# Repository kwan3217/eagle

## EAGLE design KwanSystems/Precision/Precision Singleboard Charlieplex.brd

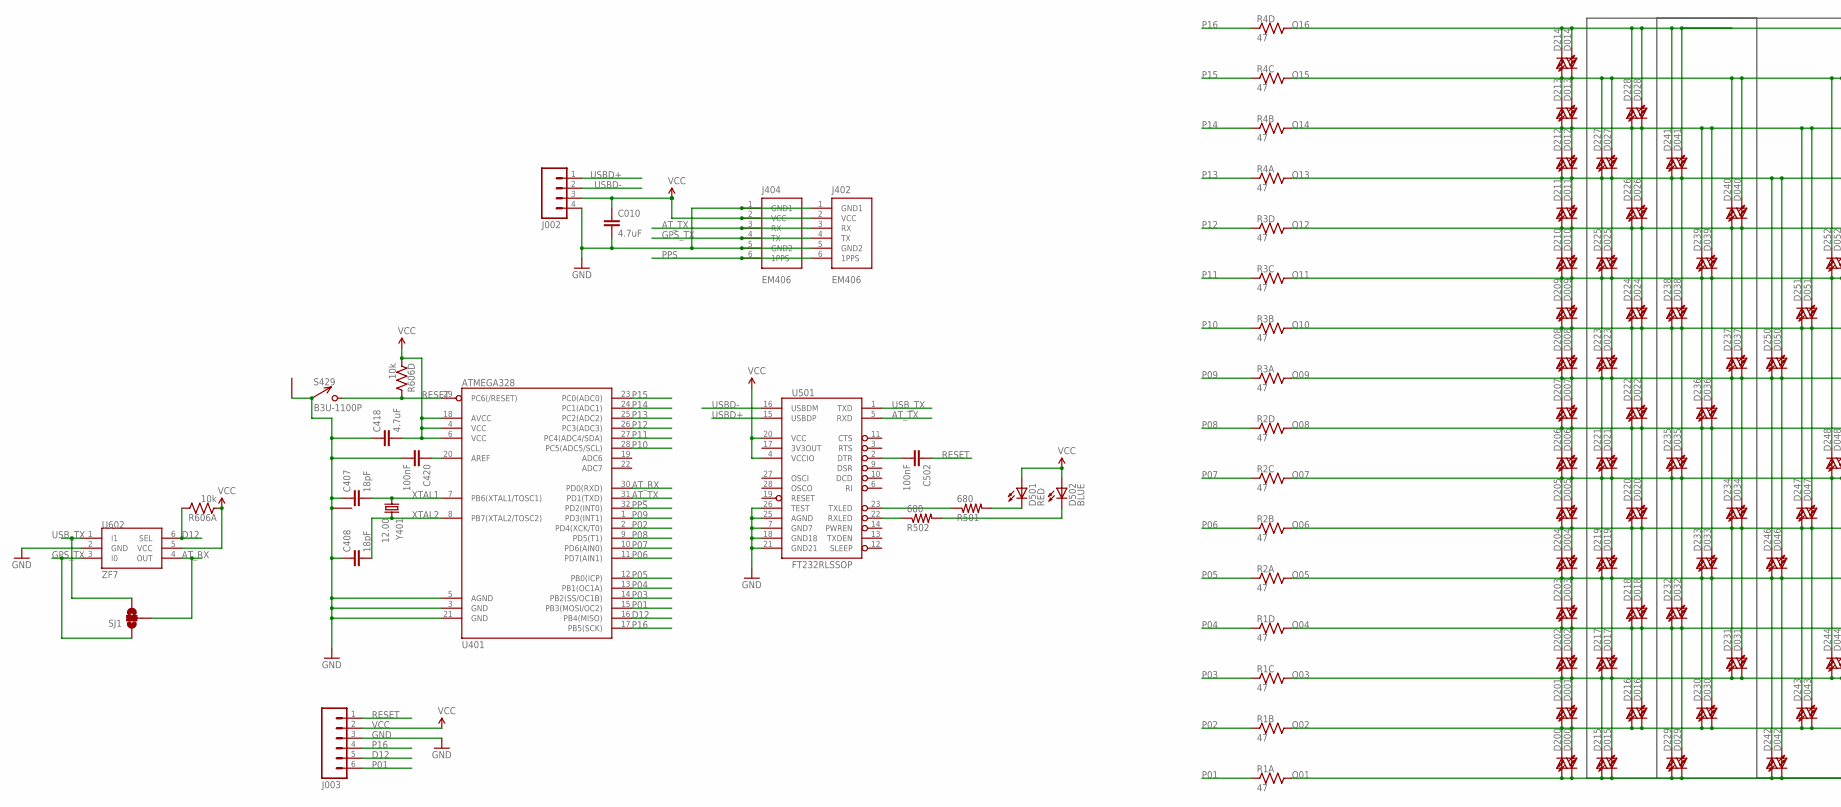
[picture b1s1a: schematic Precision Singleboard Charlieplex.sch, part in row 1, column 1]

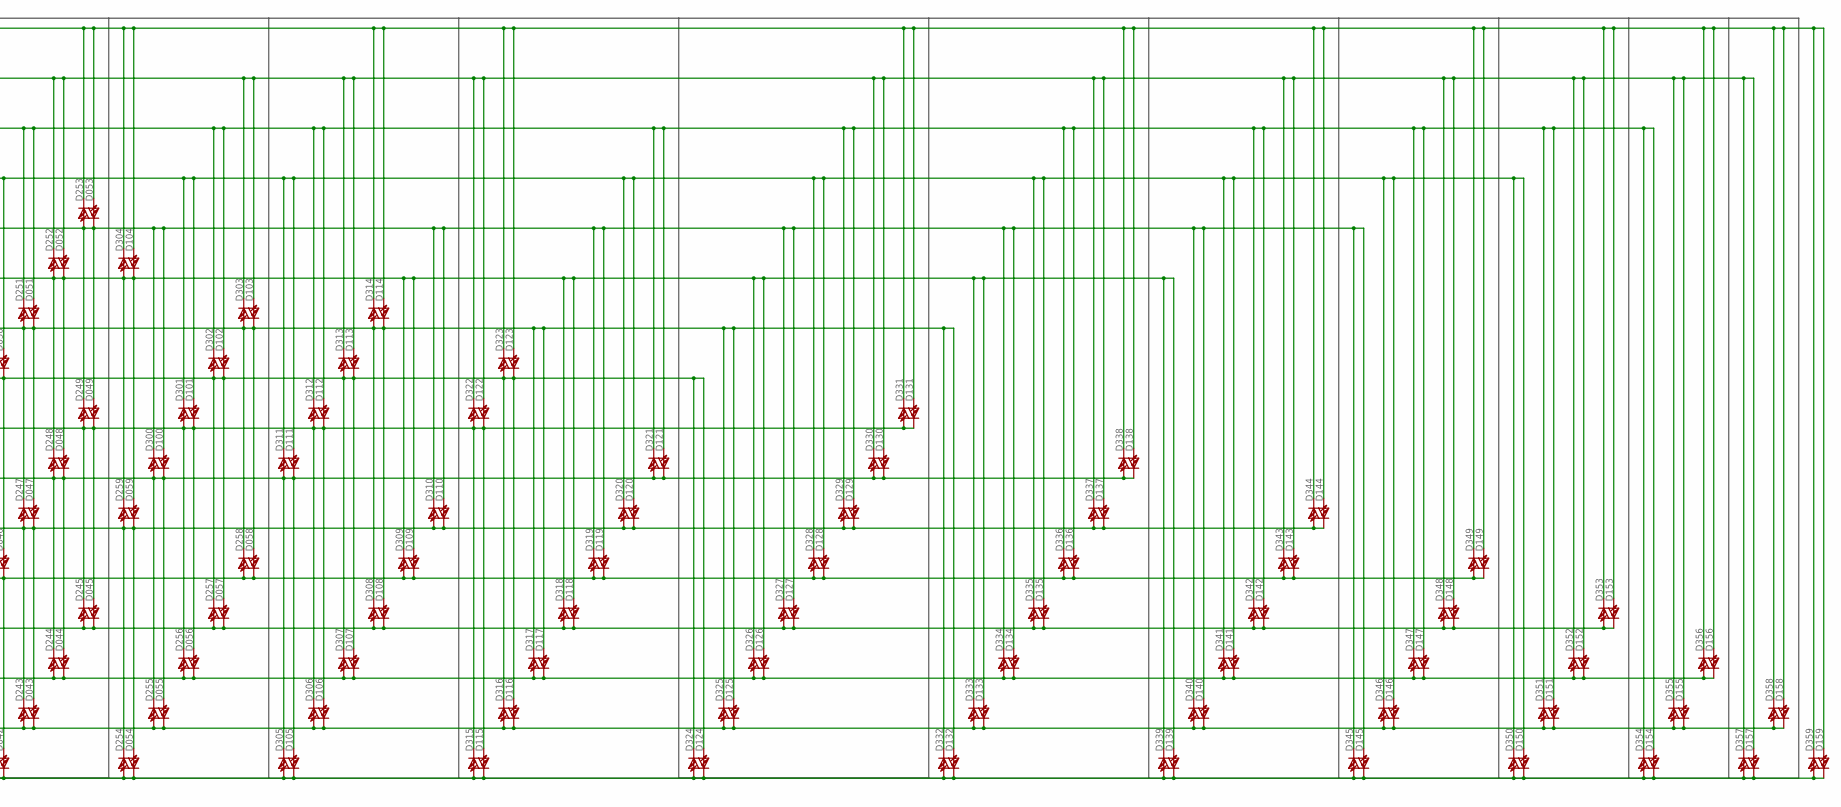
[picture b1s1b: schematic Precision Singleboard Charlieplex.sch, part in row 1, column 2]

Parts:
C010, C418: 4.7uF; 0603-CAP
C407, C408: 18pF; 0603-CAP
C420, C502: 100nF; 0603-CAP
D000, D001, D002, D003, D004, D005, D006, D007, D008, D009, D010, D011, D012, D013, D014, D015, D016, D017, D018, D019, D020, D021, D022, D023, D024, D025, D026, D027, D028, D029, D030, D031, D032, D033, D034, D035, D036, D037, D038, D039, D040, D041, D042, D043, D044, D045, D046, D047, D048, D049, D050, D051, D052, D053, D054, D055, D056, D057, D058, D059, D100, D101, D102, D103, D104, D105, D106, D107, D108, D109, D110, D111, D112, D113, D114, D115, D116, D117, D118, D119, D120, D121, D122, D123, D124, D125, D126, D127, D128, D129, D130, D131, D132, D133, D134, D135, D136, D137, D138, D139, D140, D141, D142, D143, D144, D145, D146, D147, D148, D149, D150, D151, D152, D153, D154, D155, D156, D157, D158, D159, D200, D201, D202, D203, D204, D205, D206, D207, D208, D209, D210, D211, D212, D213, D214, D215, D216, D217, D218, D219, D220, D221, D222, D223, D224, D225, D226, D227, D228, D229, D230, D231, D232, D233, D234, D235, D236, D237, D238, D239, D240, D241, D242, D243, D244, D245, D246, D247, D248, D249, D250, D251, D252, D253, D254, D255, D256, D257, D258, D259, D300, D301, D302, D303, D304, D305, D306, D307, D308, D309, D310, D311, D312, D313, D314, D315, D316, D317, D318, D319, D320, D321, D322, D323, D324, D325, D326, D327, D328, D329, D330, D331, D332, D333, D334, D335, D336, D337, D338, D339, D340, D341, D342, D343, D344, D345, D346, D347, D348, D349, D350, D351, D352, D353, D354, D355, D356, D357, D358, D359: HOUR; LED-0603
D501: RED; LED-0603
D502: BLUE; LED-0603
J002: M04PTH; 1X04
J003: M06SIP; 1X06
J402, J404: EM406
R1, R2, R3, R4: 47; CRA04
R501, R502: 680; 0603-RES
R606: 10k; CRA04
S429: B3U-1100P
SJ1: SOLDERJUMPER_2WAYS; SJ_3
U401: ATMEGA328; TQFP32-08
U501: FT232RLSSOP; SSOP28DB
U602: ZF7; SC-70-6
Y401: 12.00; CRYSTAL_SMD

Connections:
AREF: C420.1, U401.20 (AREF)
AT_RX: SJ1.2, U401.30 (PD0(RXD)), U602.4 (OUT)
AT_TX: J402.3 (RX), J404.3 (RX), U401.31 (PD1(TXD)), U501.5 (RXD)
D12: J003.5, R606.8 (2), U401.16 (PB4(MISO)), U602.6 (SEL)
GND: C010.2, C407.1, C408.1, C418.1, C420.2, J002.4, J003.3, J402.1 (GND1), J402.5 (GND2), J404.1 (GND1), J404.5 (GND2), S429.P$1 (1), S429.P$3 (1), U401.3 (GND), U401.5 (AGND), U401.21 (GND), U501.7 (GND7), U501.18 (GND18), U501.21 (GND21), U501.25 (AGND), U501.26 (TEST), U602.2 (GND), Y401.2 (1), Y401.4 (1)
GPS_TX: J402.4 (TX), J404.4 (TX), SJ1.1, U602.3 (I0)
unnamed: C502.2, U501.2 (DTR)
unnamed: D501.C, R501.2
unnamed: R501.1, U501.23 (TXLED)
unnamed: R502.1, U501.22 (RXLED)
unnamed: D502.C, R502.2
P01: J003.6, R1.1, U401.15 (PB3(MOSI/OC2))
P02: R1.2 (1), U401.2 (PD4(XCK/T0))
P03: R1.3 (1), U401.14 (PB2(SS/OC1B))
P04: R1.4 (1), U401.13 (PB1(OC1A))
P05: R2.1, U401.12 (PB0(ICP))
P06: R2.2 (1), U401.11 (PD7(AIN1))
P07: R2.3 (1), U401.10 (PD6(AIN0))
P08: R2.4 (1), U401.9 (PD5(T1))
P09: R3.1, U401.1 (PD3(INT1))
P10: R3.2 (1), U401.28 (PC5(ADC5/SCL))
P11: R3.3 (1), U401.27 (PC4(ADC4/SDA))
P12: R3.4 (1), U401.26 (PC3(ADC3))
P13: R4.1, U401.25 (PC2(ADC2))
P14: R4.2 (1), U401.24 (PC1(ADC1))
P15: R4.3 (1), U401.23 (PC0(ADC0))
P16: J003.4, R4.4 (1), U401.17 (PB5(SCK))
PPS: J402.6 (1PPS), J404.6 (1PPS), U401.32 (PD2(INT0))
Q01: D000.C, D015.C, D029.C, D042.C, D054.C, D105.C, D115.C, D124.C, D132.C, D139.C, D145.C, D150.C, D154.C, D157.C, D159.C, D200.A, D215.A, D229.A, D242.A, D254.A, D305.A, D315.A, D324.A, D332.A, D339.A, D345.A, D350.A, D354.A, D357.A, D359.A, R1.8 (2)
Q02: D000.A, D001.C, D016.C, D030.C, D043.C, D055.C, D106.C, D116.C, D125.C, D133.C, D140.C, D146.C, D151.C, D155.C, D158.C, D200.C, D201.A, D216.A, D230.A, D243.A, D255.A, D306.A, D316.A, D325.A, D333.A, D340.A, D346.A, D351.A, D355.A, D358.A, R1.7 (2)
Q03: D001.A, D002.C, D015.A, D017.C, D031.C, D044.C, D056.C, D107.C, D117.C, D126.C, D134.C, D141.C, D147.C, D152.C, D156.C, D201.C, D202.A, D215.C, D217.A, D231.A, D244.A, D256.A, D307.A, D317.A, D326.A, D334.A, D341.A, D347.A, D352.A, D356.A, R1.6 (2)
Q04: D002.A, D003.C, D016.A, D018.C, D029.A, D032.C, D045.C, D057.C, D108.C, D118.C, D127.C, D135.C, D142.C, D148.C, D153.C, D202.C, D203.A, D216.C, D218.A, D229.C, D232.A, D245.A, D257.A, D308.A, D318.A, D327.A, D335.A, D342.A, D348.A, D353.A, R1.5 (2)
Q05: D003.A, D004.C, D017.A, D019.C, D030.A, D033.C, D042.A, D046.C, D058.C, D109.C, D119.C, D128.C, D136.C, D143.C, D149.C, D203.C, D204.A, D217.C, D219.A, D230.C, D233.A, D242.C, D246.A, D258.A, D309.A, D319.A, D328.A, D336.A, D343.A, D349.A, R2.8 (2)
Q06: D004.A, D005.C, D018.A, D020.C, D031.A, D034.C, D043.A, D047.C, D054.A, D059.C, D110.C, D120.C, D129.C, D137.C, D144.C, D204.C, D205.A, D218.C, D220.A, D231.C, D234.A, D243.C, D247.A, D254.C, D259.A, D310.A, D320.A, D329.A, D337.A, D344.A, R2.7 (2)
Q07: D005.A, D006.C, D019.A, D021.C, D032.A, D035.C, D044.A, D048.C, D055.A, D100.C, D105.A, D111.C, D121.C, D130.C, D138.C, D205.C, D206.A, D219.C, D221.A, D232.C, D235.A, D244.C, D248.A, D255.C, D300.A, D305.C, D311.A, D321.A, D330.A, D338.A, R2.6 (2)
Q08: D006.A, D007.C, D020.A, D022.C, D033.A, D036.C, D045.A, D049.C, D056.A, D101.C, D106.A, D112.C, D115.A, D122.C, D131.C, D206.C, D207.A, D220.C, D222.A, D233.C, D236.A, D245.C, D249.A, D256.C, D301.A, D306.C, D312.A, D315.C, D322.A, D331.A, R2.5 (2)
Q09: D007.A, D008.C, D021.A, D023.C, D034.A, D037.C, D046.A, D050.C, D057.A, D102.C, D107.A, D113.C, D116.A, D123.C, D124.A, D207.C, D208.A, D221.C, D223.A, D234.C, D237.A, D246.C, D250.A, D257.C, D302.A, D307.C, D313.A, D316.C, D323.A, D324.C, R3.8 (2)
Q10: D008.A, D009.C, D022.A, D024.C, D035.A, D038.C, D047.A, D051.C, D058.A, D103.C, D108.A, D114.C, D117.A, D125.A, D132.A, D208.C, D209.A, D222.C, D224.A, D235.C, D238.A, D247.C, D251.A, D258.C, D303.A, D308.C, D314.A, D317.C, D325.C, D332.C, R3.7 (2)
Q11: D009.A, D010.C, D023.A, D025.C, D036.A, D039.C, D048.A, D052.C, D059.A, D104.C, D109.A, D118.A, D126.A, D133.A, D139.A, D209.C, D210.A, D223.C, D225.A, D236.C, D239.A, D248.C, D252.A, D259.C, D304.A, D309.C, D318.C, D326.C, D333.C, D339.C, R3.6 (2)
Q12: D010.A, D011.C, D024.A, D026.C, D037.A, D040.C, D049.A, D053.C, D100.A, D110.A, D119.A, D127.A, D134.A, D140.A, D145.A, D210.C, D211.A, D224.C, D226.A, D237.C, D240.A, D249.C, D253.A, D300.C, D310.C, D319.C, D327.C, D334.C, D340.C, D345.C, R3.5 (2)
Q13: D011.A, D012.C, D025.A, D027.C, D038.A, D041.C, D050.A, D101.A, D111.A, D120.A, D128.A, D135.A, D141.A, D146.A, D150.A, D211.C, D212.A, D225.C, D227.A, D238.C, D241.A, D250.C, D301.C, D311.C, D320.C, D328.C, D335.C, D341.C, D346.C, D350.C, R4.8 (2)
Q14: D012.A, D013.C, D026.A, D028.C, D039.A, D051.A, D102.A, D112.A, D121.A, D129.A, D136.A, D142.A, D147.A, D151.A, D154.A, D212.C, D213.A, D226.C, D228.A, D239.C, D251.C, D302.C, D312.C, D321.C, D329.C, D336.C, D342.C, D347.C, D351.C, D354.C, R4.7 (2)
Q15: D013.A, D014.C, D027.A, D040.A, D052.A, D103.A, D113.A, D122.A, D130.A, D137.A, D143.A, D148.A, D152.A, D155.A, D157.A, D213.C, D214.A, D227.C, D240.C, D252.C, D303.C, D313.C, D322.C, D330.C, D337.C, D343.C, D348.C, D352.C, D355.C, D357.C, R4.6 (2)
Q16: D014.A, D028.A, D041.A, D053.A, D104.A, D114.A, D123.A, D131.A, D138.A, D144.A, D149.A, D153.A, D156.A, D158.A, D159.A, D214.C, D228.C, D241.C, D253.C, D304.C, D314.C, D323.C, D331.C, D338.C, D344.C, D349.C, D353.C, D356.C, D358.C, D359.C, R4.5 (2)
RESET: C502.1, J003.1, R606.5 (2), S429.P$2 (2), U401.29 (PC6(/RESET))
USBD+: J002.1, U501.15 (USBDP)
USBD-: J002.2, U501.16 (USBDM)
USB_TX: SJ1.3, U501.1 (TXD), U602.1 (I1)
VCC: C010.1, C418.2, D501.A, D502.A, J002.3, J003.2, J402.2 (VCC), J404.2 (VCC), R606.1, R606.4 (1), U401.4 (VCC), U401.6 (VCC), U401.18 (AVCC), U501.4 (VCCIO), U501.20 (VCC), U602.5 (VCC)
XTAL1: C407.2, U401.7 (PB6(XTAL1/TOSC1)), Y401.1
XTAL2: C408.2, U401.8 (PB7(XTAL2/TOSC2)), Y401.3 (2)

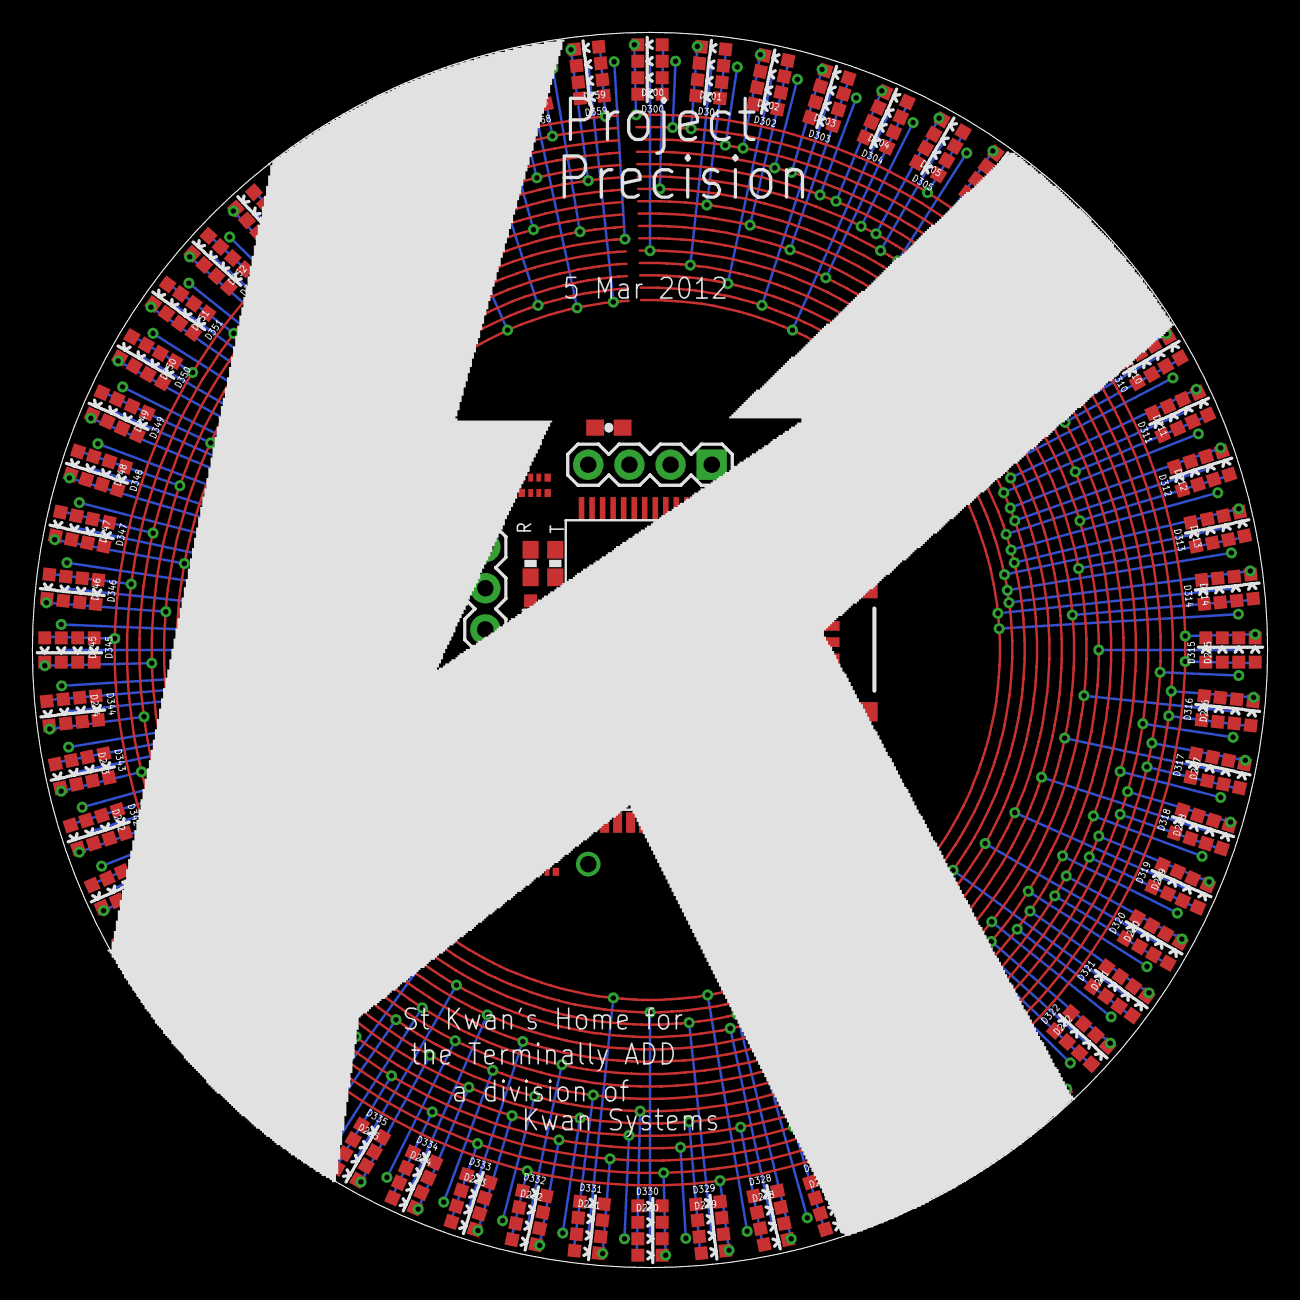
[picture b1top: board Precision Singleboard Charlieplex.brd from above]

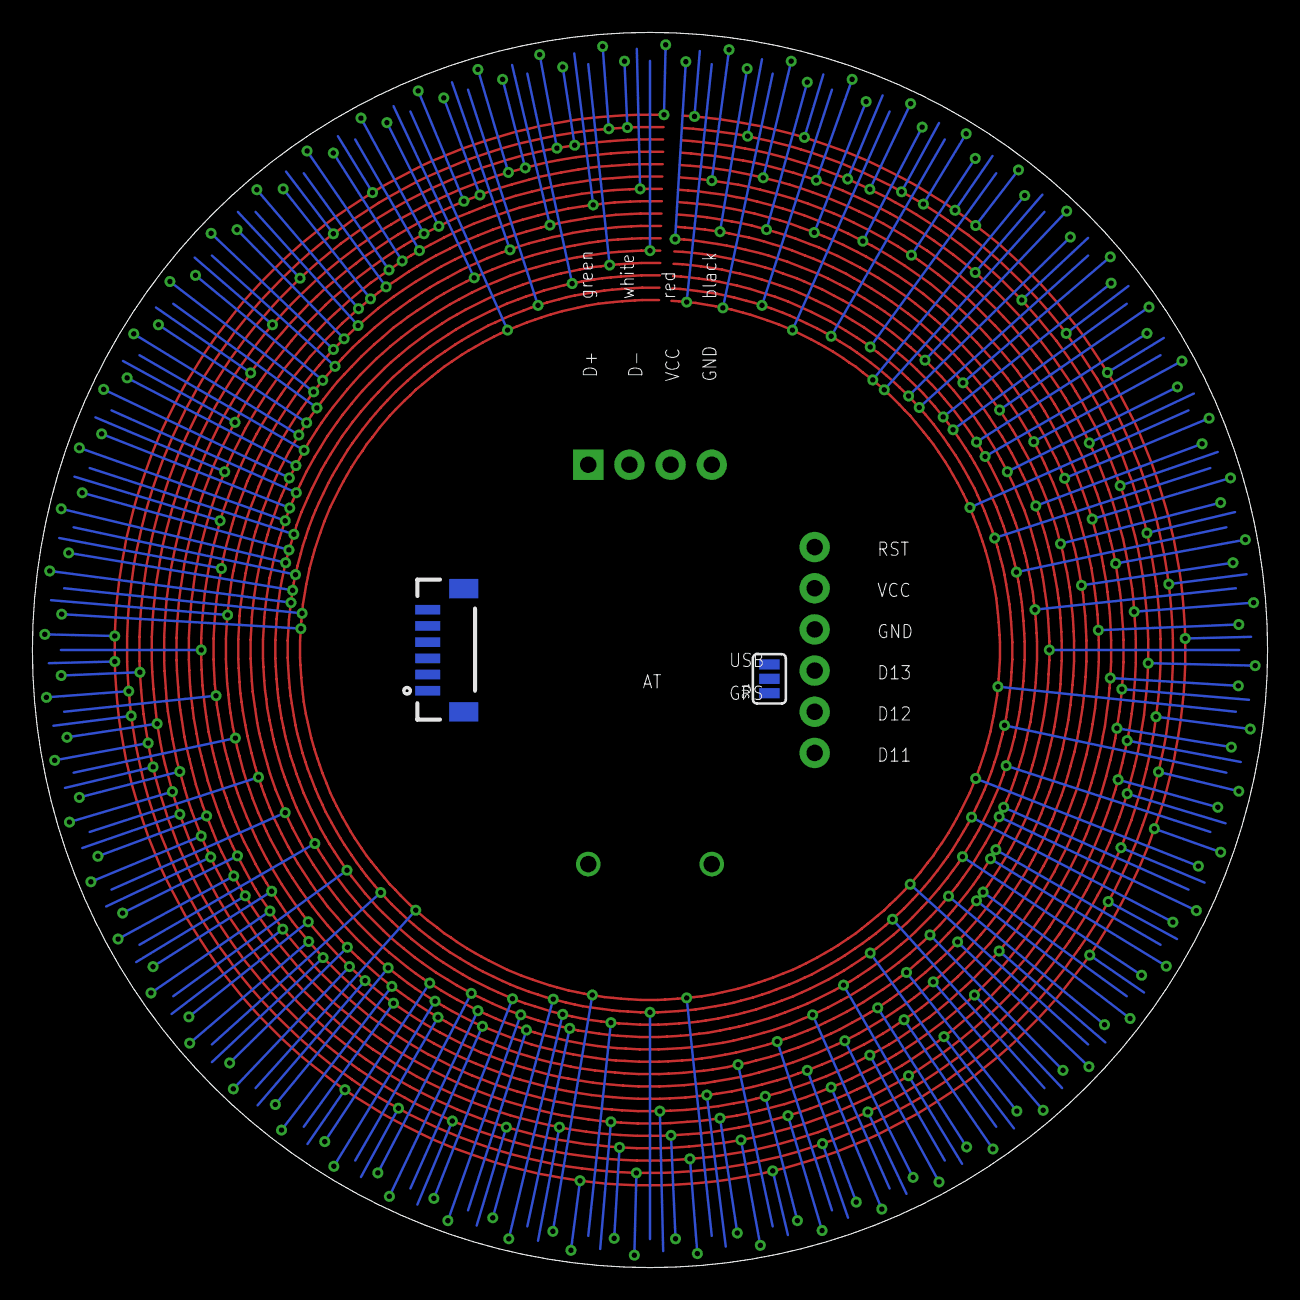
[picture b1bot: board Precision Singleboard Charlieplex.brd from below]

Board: 2 copper layers, 76.2 x 76.2 mm, 265 parts (2 on the bottom side), 51 nets.

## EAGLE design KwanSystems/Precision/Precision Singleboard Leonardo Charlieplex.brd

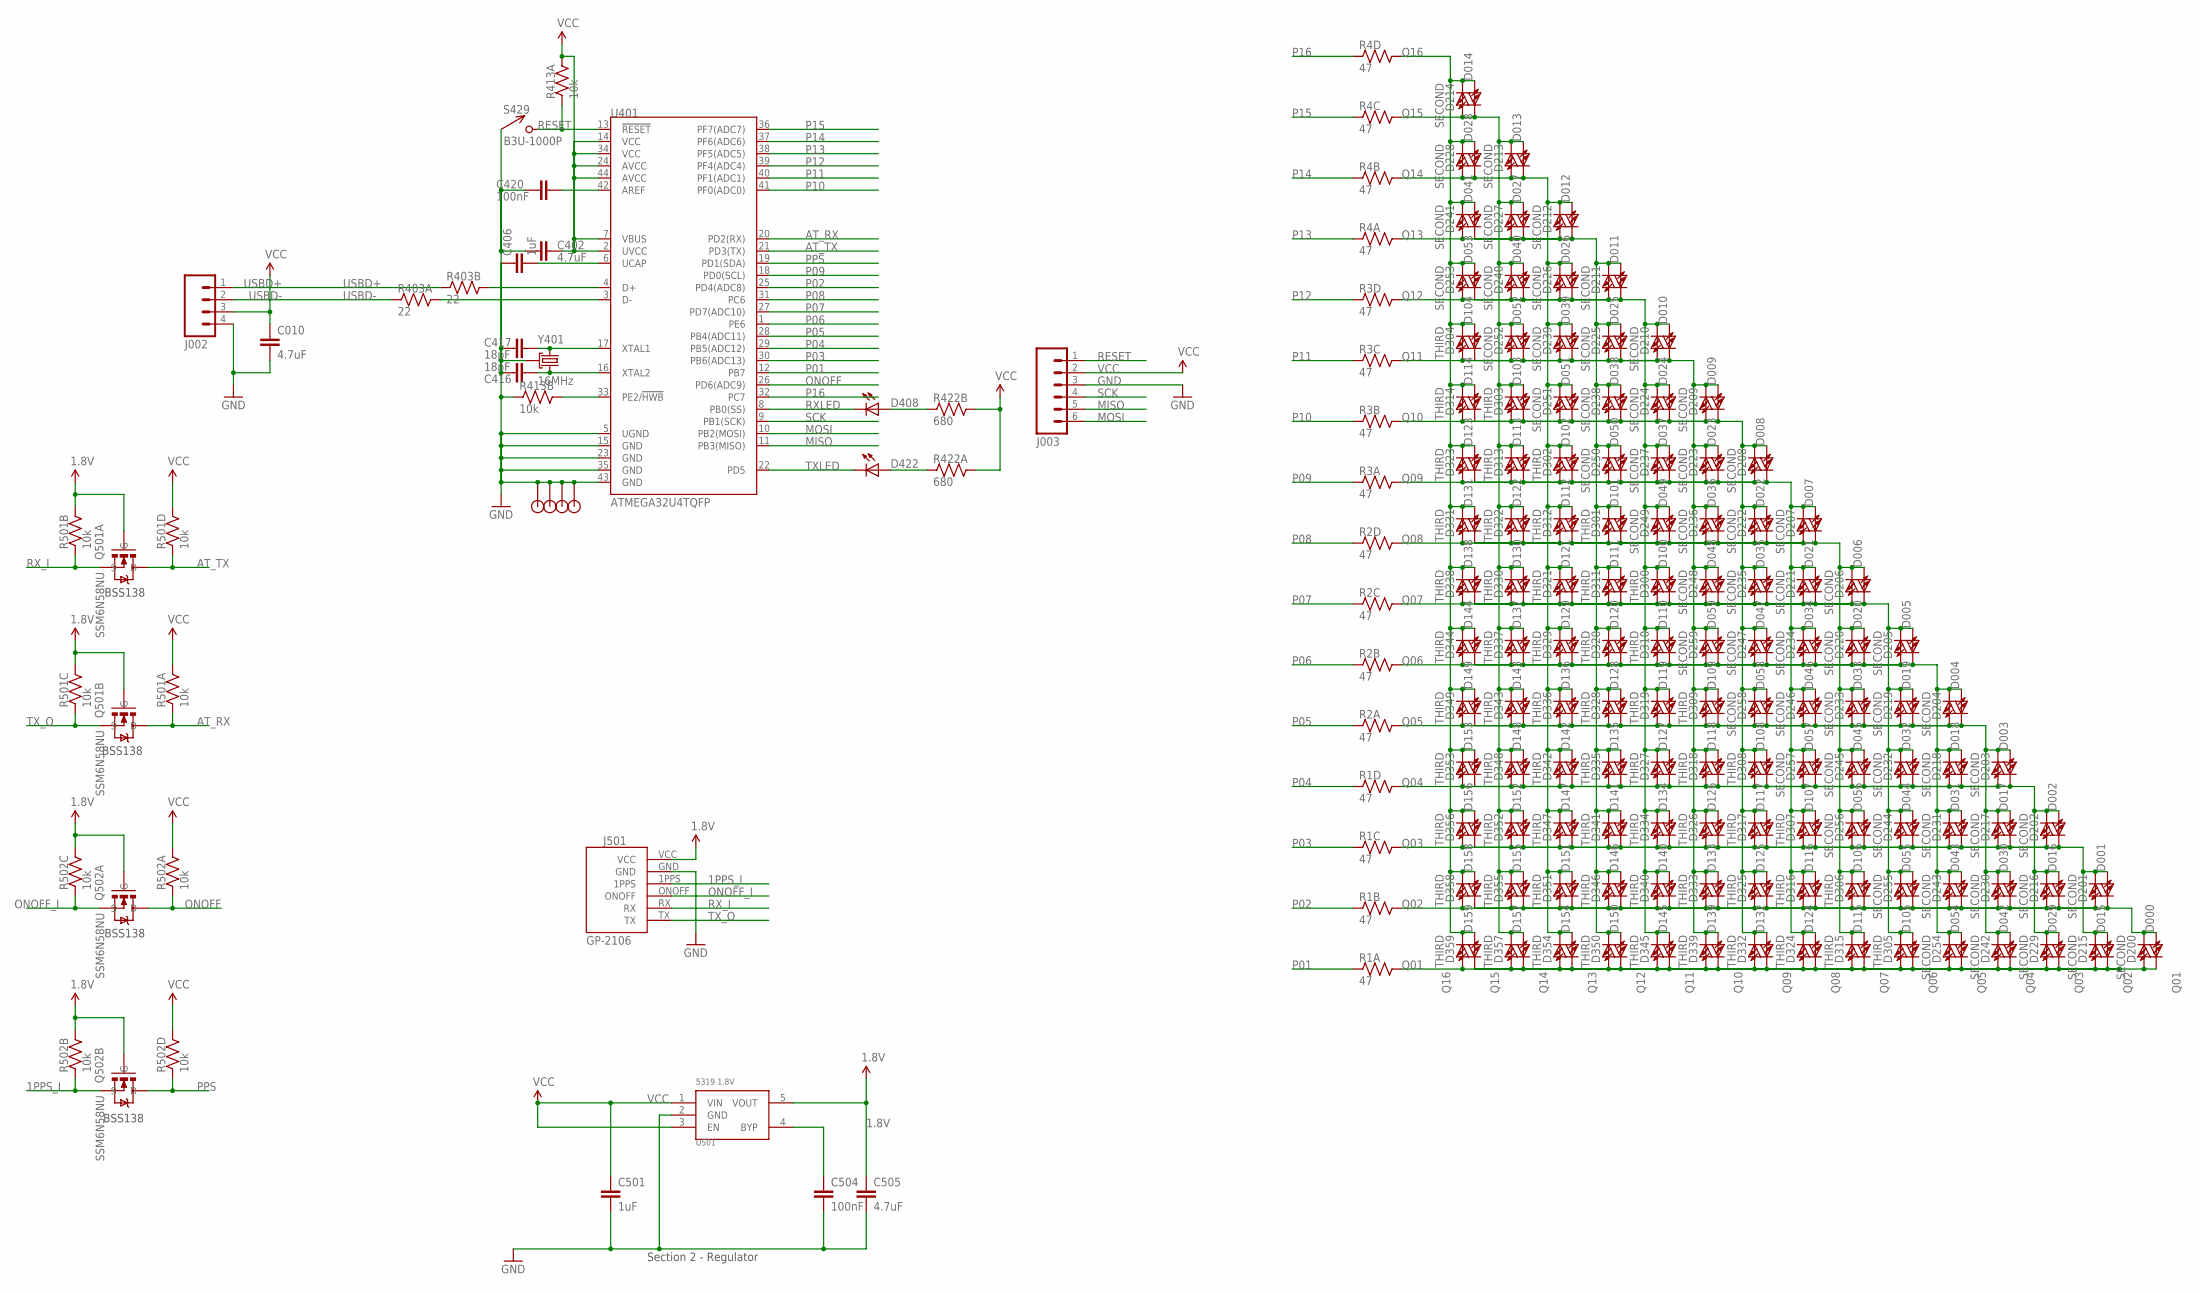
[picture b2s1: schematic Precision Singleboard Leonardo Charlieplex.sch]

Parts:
C010, C402: 4.7uF; 0603-CAP
C406, C501: 1uF; 0603-CAP; DIGIKEY 445-4114-1-ND
C416, C417: 18pF; 0603-CAP
C420: 100nF; 0603-CAP
C504: 100nF; 0603-CAP; DIGIKEY 445-1265-1-ND
C505: 4.7uF; 0603-CAP; DIGIKEY 445-7395-1-ND
D000, D001, D002, D003, D004, D005, D006, D007, D008, D009, D010, D011, D012, D013, D014, D015, D016, D017, D018, D019, D020, D021, D022, D023, D024, D025, D026, D027, D028, D029, D030, D031, D032, D033, D034, D035, D036, D037, D038, D039, D040, D041, D042, D043, D044, D045, D046, D047, D048, D049, D050, D051, D052, D053, D054, D055, D056, D057, D058, D059: HOUR; LED-0603
D100, D101, D102, D103, D104, D105, D106, D107, D108, D109, D110, D111, D112, D113, D114, D115, D116, D117, D118, D119, D120, D121, D122, D123, D124, D125, D126, D127, D128, D129, D130, D131, D132, D133, D134, D135, D136, D137, D138, D139, D140, D141, D142, D143, D144, D145, D146, D147, D148, D149, D150, D151, D152, D153, D154, D155, D156, D157, D158, D159: MINUTE; LED-0603
D200, D201, D202, D203, D204, D205, D206, D207, D208, D209, D210, D211, D212, D213, D214, D215, D216, D217, D218, D219, D220, D221, D222, D223, D224, D225, D226, D227, D228, D229, D230, D231, D232, D233, D234, D235, D236, D237, D238, D239, D240, D241, D242, D243, D244, D245, D246, D247, D248, D249, D250, D251, D252, D253, D254, D255, D256, D257, D258, D259: SECOND; LED-0603
D300, D301, D302, D303, D304, D305, D306, D307, D308, D309, D310, D311, D312, D313, D314, D315, D316, D317, D318, D319, D320, D321, D322, D323, D324, D325, D326, D327, D328, D329, D330, D331, D332, D333, D334, D335, D336, D337, D338, D339, D340, D341, D342, D343, D344, D345, D346, D347, D348, D349, D350, D351, D352, D353, D354, D355, D356, D357, D358, D359: THIRD; LED-0603
D408: RED; LED-0603
D422: BLUE; LED-0603
J002: M04PTH; 1X04
J003: M06SIP; 1X06
J501: GP-2106
JP1, JP2, JP3, JP4: STANDOFF
Q501, Q502: SSM6N58NU; UDFN6
R1, R2, R3, R4: 47; CRA04
R403: 22; CRA02
R413: 10k; CRA02
R422: 680; CRA02
R501, R502: 10k; CRA04; DIGIKEY CRA4S810KCT-ND
S429: B3U-1000P
U401: ATMEGA32U4TQFP; SPARKFUN-DIGITALIC_TQFP44
U501: 5319 1.8V; SOT-23-5; DIGIKEY 576-1910-1-ND
Y401: 16MHz; CRYSTAL_SMD

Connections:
1.8V: C505.1, J501.VCC, Q501.2 (G), Q501.5 (G), Q502.2 (G), Q502.5 (G), R501.6 (2), R501.7 (2), R502.6 (2), R502.7 (2), U501.5 (VOUT)
1PPS_I: J501.1PPS, Q502.4 (S), R502.2 (1)
AREF: C420.1, U401.42 (AREF)
AT_RX: Q501.3 (D), R501.1, U401.20 (PD2(RX))
AT_TX: Q501.6 (D), R501.4 (1), U401.21 (PD3(TX))
GND: C010.2, C402.1, C406.1, C416.1, C417.1, C420.2, C501.2, C504.2, C505.2, J002.4, J003.3, J501.GND, JP1.P$1, JP2.P$1, JP3.P$1, JP4.P$1, R413.2 (1), S429.P$1 (1), U401.5 (UGND), U401.15 (GND), U401.23 (GND), U401.35 (GND), U401.43 (GND), U501.2 (GND), Y401.2 (GND), Y401.4 (GND)
MISO: J003.5, U401.11 (PB3(MISO))
MOSI: J003.6, U401.10 (PB2(MOSI))
unnamed: C406.2, U401.6 (UCAP)
unnamed: R413.3 (2), U401.33 (PE2/!HWB)
unnamed: D422.A, R422.1
unnamed: D408.A, R422.2 (1)
unnamed: C504.1, U501.4 (BYP)
ONOFF: Q502.6 (D), R502.1, U401.26 (PD6(ADC9))
ONOFF_I: J501.ONOFF, Q502.1 (S), R502.3 (1)
P01: R1.1, U401.12 (PB7)
P02: R1.2 (1), U401.25 (PD4(ADC8))
P03: R1.3 (1), U401.30 (PB6(ADC13))
P04: R1.4 (1), U401.29 (PB5(ADC12))
P05: R2.1, U401.28 (PB4(ADC11))
P06: R2.2 (1), U401.1 (PE6)
P07: R2.3 (1), U401.27 (PD7(ADC10))
P08: R2.4 (1), U401.31 (PC6)
P09: R3.1, U401.18 (PD0(SCL))
P10: R3.2 (1), U401.41 (PF0(ADC0))
P11: R3.3 (1), U401.40 (PF1(ADC1))
P12: R3.4 (1), U401.39 (PF4(ADC4))
P13: R4.1, U401.38 (PF5(ADC5))
P14: R4.2 (1), U401.37 (PF6(ADC6))
P15: R4.3 (1), U401.36 (PF7(ADC7))
P16: R4.4 (1), U401.32 (PC7)
PPS: Q502.3 (D), R502.4 (1), U401.19 (PD1(SDA))
Q01: D000.C, D015.C, D029.C, D042.C, D054.C, D105.C, D115.C, D124.C, D132.C, D139.C, D145.C, D150.C, D154.C, D157.C, D159.C, D200.A, D215.A, D229.A, D242.A, D254.A, D305.A, D315.A, D324.A, D332.A, D339.A, D345.A, D350.A, D354.A, D357.A, D359.A, R1.8 (2)
Q02: D000.A, D001.C, D016.C, D030.C, D043.C, D055.C, D106.C, D116.C, D125.C, D133.C, D140.C, D146.C, D151.C, D155.C, D158.C, D200.C, D201.A, D216.A, D230.A, D243.A, D255.A, D306.A, D316.A, D325.A, D333.A, D340.A, D346.A, D351.A, D355.A, D358.A, R1.7 (2)
Q03: D001.A, D002.C, D015.A, D017.C, D031.C, D044.C, D056.C, D107.C, D117.C, D126.C, D134.C, D141.C, D147.C, D152.C, D156.C, D201.C, D202.A, D215.C, D217.A, D231.A, D244.A, D256.A, D307.A, D317.A, D326.A, D334.A, D341.A, D347.A, D352.A, D356.A, R1.6 (2)
Q04: D002.A, D003.C, D016.A, D018.C, D029.A, D032.C, D045.C, D057.C, D108.C, D118.C, D127.C, D135.C, D142.C, D148.C, D153.C, D202.C, D203.A, D216.C, D218.A, D229.C, D232.A, D245.A, D257.A, D308.A, D318.A, D327.A, D335.A, D342.A, D348.A, D353.A, R1.5 (2)
Q05: D003.A, D004.C, D017.A, D019.C, D030.A, D033.C, D042.A, D046.C, D058.C, D109.C, D119.C, D128.C, D136.C, D143.C, D149.C, D203.C, D204.A, D217.C, D219.A, D230.C, D233.A, D242.C, D246.A, D258.A, D309.A, D319.A, D328.A, D336.A, D343.A, D349.A, R2.8 (2)
Q06: D004.A, D005.C, D018.A, D020.C, D031.A, D034.C, D043.A, D047.C, D054.A, D059.C, D110.C, D120.C, D129.C, D137.C, D144.C, D204.C, D205.A, D218.C, D220.A, D231.C, D234.A, D243.C, D247.A, D254.C, D259.A, D310.A, D320.A, D329.A, D337.A, D344.A, R2.7 (2)
Q07: D005.A, D006.C, D019.A, D021.C, D032.A, D035.C, D044.A, D048.C, D055.A, D100.C, D105.A, D111.C, D121.C, D130.C, D138.C, D205.C, D206.A, D219.C, D221.A, D232.C, D235.A, D244.C, D248.A, D255.C, D300.A, D305.C, D311.A, D321.A, D330.A, D338.A, R2.6 (2)
Q08: D006.A, D007.C, D020.A, D022.C, D033.A, D036.C, D045.A, D049.C, D056.A, D101.C, D106.A, D112.C, D115.A, D122.C, D131.C, D206.C, D207.A, D220.C, D222.A, D233.C, D236.A, D245.C, D249.A, D256.C, D301.A, D306.C, D312.A, D315.C, D322.A, D331.A, R2.5 (2)
Q09: D007.A, D008.C, D021.A, D023.C, D034.A, D037.C, D046.A, D050.C, D057.A, D102.C, D107.A, D113.C, D116.A, D123.C, D124.A, D207.C, D208.A, D221.C, D223.A, D234.C, D237.A, D246.C, D250.A, D257.C, D302.A, D307.C, D313.A, D316.C, D323.A, D324.C, R3.8 (2)
Q10: D008.A, D009.C, D022.A, D024.C, D035.A, D038.C, D047.A, D051.C, D058.A, D103.C, D108.A, D114.C, D117.A, D125.A, D132.A, D208.C, D209.A, D222.C, D224.A, D235.C, D238.A, D247.C, D251.A, D258.C, D303.A, D308.C, D314.A, D317.C, D325.C, D332.C, R3.7 (2)
Q11: D009.A, D010.C, D023.A, D025.C, D036.A, D039.C, D048.A, D052.C, D059.A, D104.C, D109.A, D118.A, D126.A, D133.A, D139.A, D209.C, D210.A, D223.C, D225.A, D236.C, D239.A, D248.C, D252.A, D259.C, D304.A, D309.C, D318.C, D326.C, D333.C, D339.C, R3.6 (2)
Q12: D010.A, D011.C, D024.A, D026.C, D037.A, D040.C, D049.A, D053.C, D100.A, D110.A, D119.A, D127.A, D134.A, D140.A, D145.A, D210.C, D211.A, D224.C, D226.A, D237.C, D240.A, D249.C, D253.A, D300.C, D310.C, D319.C, D327.C, D334.C, D340.C, D345.C, R3.5 (2)
Q13: D011.A, D012.C, D025.A, D027.C, D038.A, D041.C, D050.A, D101.A, D111.A, D120.A, D128.A, D135.A, D141.A, D146.A, D150.A, D211.C, D212.A, D225.C, D227.A, D238.C, D241.A, D250.C, D301.C, D311.C, D320.C, D328.C, D335.C, D341.C, D346.C, D350.C, R4.8 (2)
Q14: D012.A, D013.C, D026.A, D028.C, D039.A, D051.A, D102.A, D112.A, D121.A, D129.A, D136.A, D142.A, D147.A, D151.A, D154.A, D212.C, D213.A, D226.C, D228.A, D239.C, D251.C, D302.C, D312.C, D321.C, D329.C, D336.C, D342.C, D347.C, D351.C, D354.C, R4.7 (2)
Q15: D013.A, D014.C, D027.A, D040.A, D052.A, D103.A, D113.A, D122.A, D130.A, D137.A, D143.A, D148.A, D152.A, D155.A, D157.A, D213.C, D214.A, D227.C, D240.C, D252.C, D303.C, D313.C, D322.C, D330.C, D337.C, D343.C, D348.C, D352.C, D355.C, D357.C, R4.6 (2)
Q16: D014.A, D028.A, D041.A, D053.A, D104.A, D114.A, D123.A, D131.A, D138.A, D144.A, D149.A, D153.A, D156.A, D158.A, D159.A, D214.C, D228.C, D241.C, D253.C, D304.C, D314.C, D323.C, D331.C, D338.C, D344.C, D349.C, D353.C, D356.C, D358.C, D359.C, R4.5 (2)
RD+: R403.3 (2), U401.4 (D+)
RD-: R403.4 (2), U401.3 (D-)
RESET: J003.1, R413.1, S429.P$2 (2), U401.13 (!RESET)
RXLED: D408.C, U401.8 (PB0(SS))
RX_I: J501.RX, Q501.1 (S), R501.2 (1)
SCK: J003.4, U401.9 (PB1(SCK))
TXLED: D422.C, U401.22 (PD5)
TX_O: J501.TX, Q501.4 (S), R501.3 (1)
USBD+: J002.1, R403.2 (1)
USBD-: J002.2, R403.1
VCC: C010.1, C402.2, C501.1, J002.3, J003.2, R413.4 (2), R422.3 (2), R422.4 (2), R501.5 (2), R501.8 (2), R502.5 (2), R502.8 (2), U401.2 (UVCC), U401.7 (VBUS), U401.14 (VCC), U401.24 (AVCC), U401.34 (VCC), U401.44 (AVCC), U501.1 (VIN), U501.3 (EN)
XTAL1: C417.2, U401.17 (XTAL1), Y401.1
XTAL2: C416.2, U401.16 (XTAL2), Y401.3 (2)

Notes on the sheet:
BSS138
Section 2 - Regulator

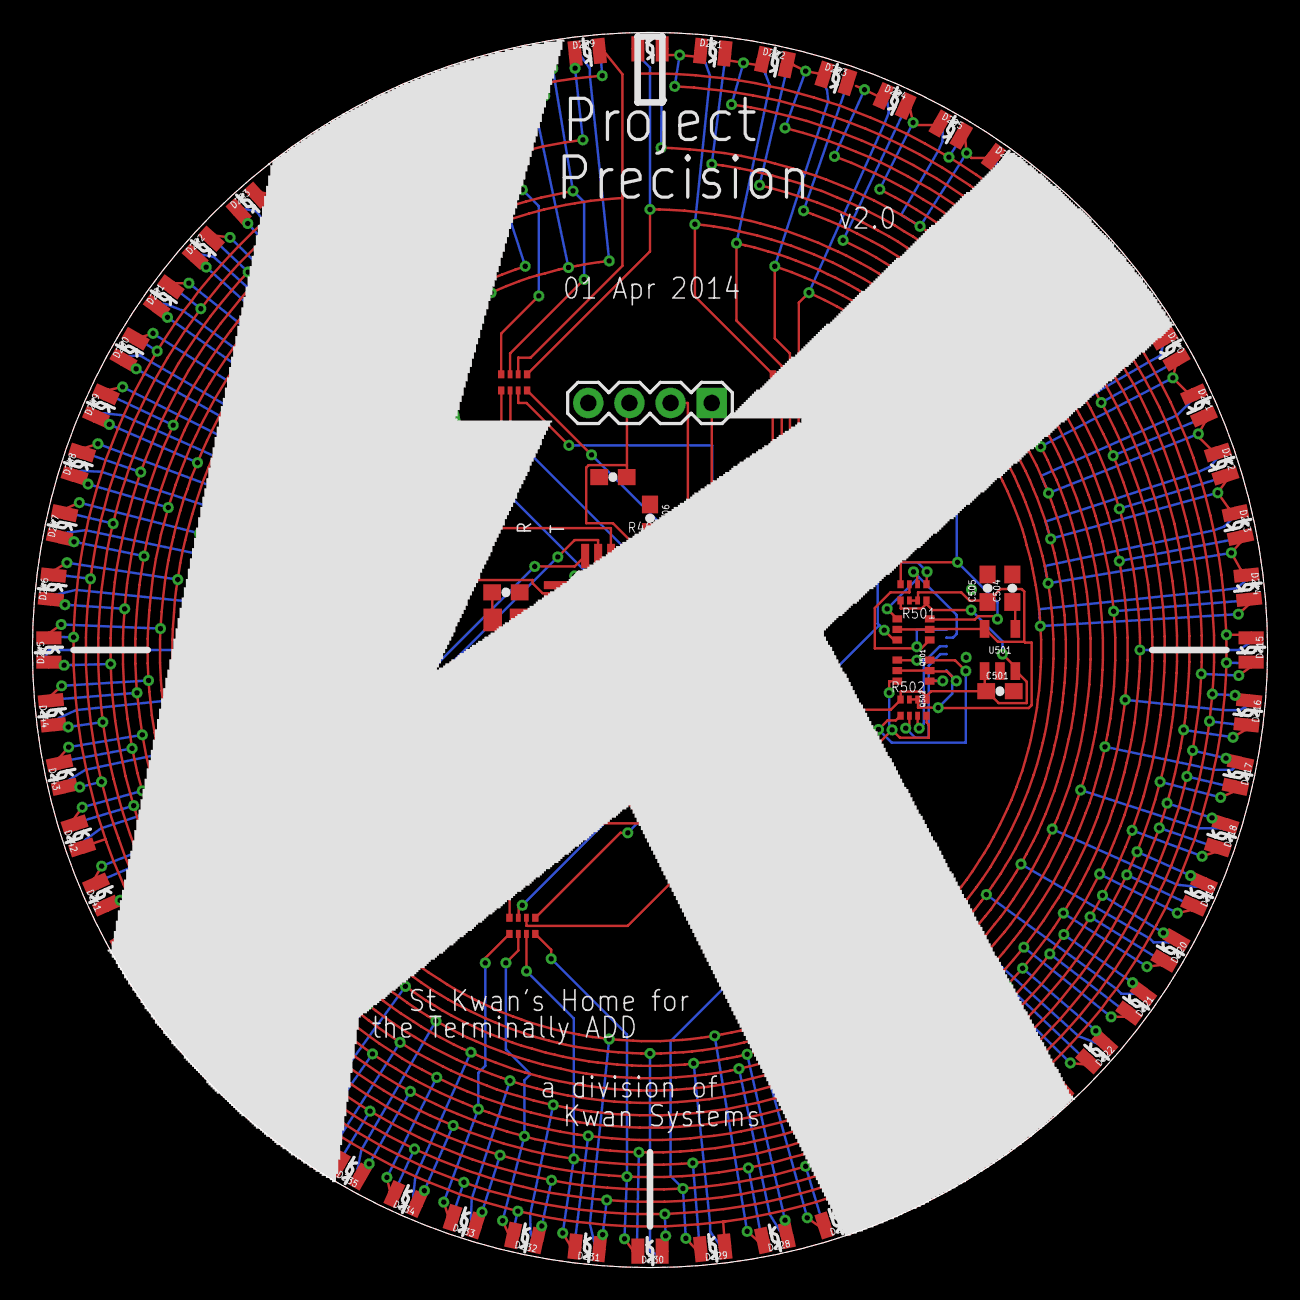
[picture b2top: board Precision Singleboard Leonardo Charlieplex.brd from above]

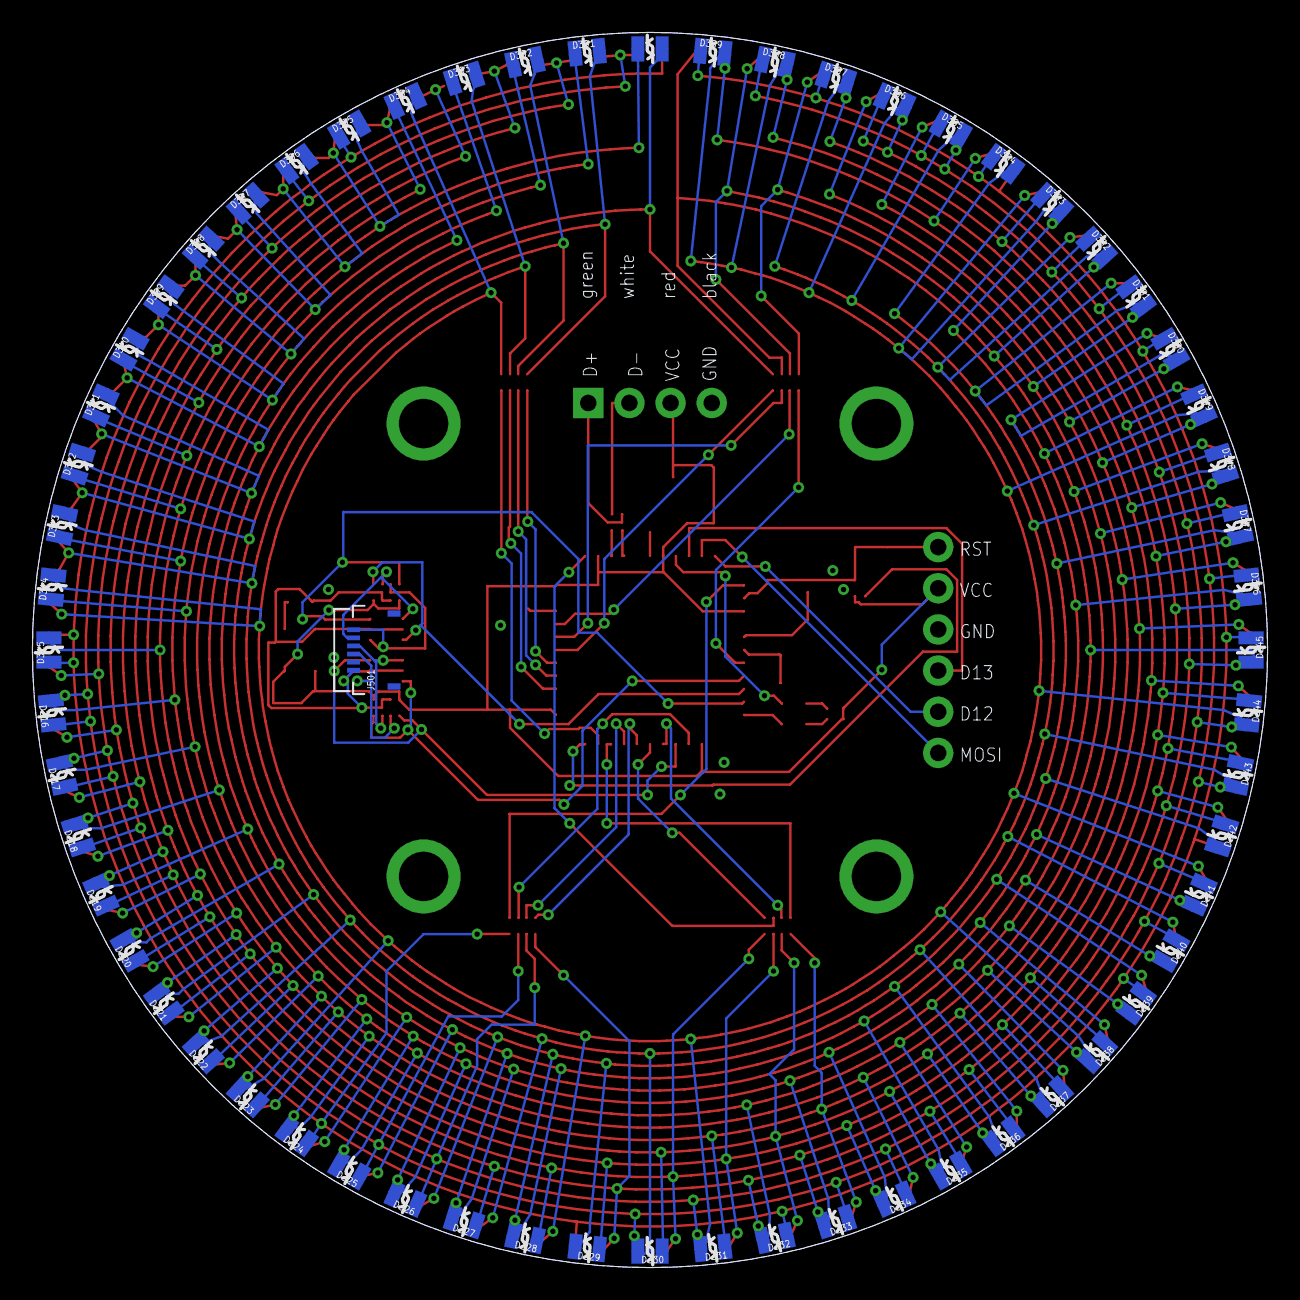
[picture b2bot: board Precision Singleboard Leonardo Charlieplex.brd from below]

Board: 2 copper layers, 76.2 x 76.2 mm, 273 parts (121 on the bottom side), 61 nets.

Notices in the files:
parts and their libraries:
SparkFun-DigitalIC: Licensing: CC v3.0 Share-Alike You are welcome to use this library for commercial purposes.
